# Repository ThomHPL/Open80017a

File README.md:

# Open80017a: an Open Source 80017a Roland Clone
<table>
  <tr>
    <td align="center"><b>Top View</b><br></td>
    <td align="center"><b>Bottom View</b><br></td>
  </tr>
</table>

## Context
The 80017a is a VCF/VCA module encapsulated in resin, used in the voices of various vintage Roland synthesizers such as the Juno-106. These modules are known to fail over time, potentially due to the resin coating.

## Open Source Aftermarket Replacement
While some clone modules are available for sale, they are often hard to find or relatively expensive. To be 100% honest, this project is also mostly a learning opportunity for me in vintage analog synth design.

### Key Design Focus Points
- **EMC Best Practices**
    - 4-layer PCB design
    - Proper trace spacing
- **Thermal Stability**
    - Vias under the OTAs to (try to) thermally couple them using an internal ground plane
- **Miniaturization**
    - Tries to match the original module dimensions

### Schematic

### Production
While the project uses a 4-layer board design, it has not requirements considering impedance control. It can therefore be made with any cheap 4-layer online service.

## Tests
Version 0.1 was assembled and tested in a Juno-106, with no perceivable difference (to my ears) between the clone and the original voices. However, there was an error in the buffer PMOS footprint, which was corrected with bodge wires.

Version 0.2 fixes the footprints. It has not yet been assembled or tested.

## Support

If you like my work, you can contribute with a coffee there ;)

## Credits
- This work was motivated by a dead channel on my brother's Juno-106. Thanks for the opportunity to help bro'!
- It would not have been possible without resources found online, especially the information provided by **dksynth** and **guest** on the following forum. Many thanks to them! [https://modwiggler.com/forum/viewtopic.php?t=238335](https://modwiggler.com/forum/viewtopic.php?t=238335)
- Thanks to [**deanm1278**](https://github.com/deanm1278) for the [LM13700 spice model](https://github.com/deanm1278/LM13700-spice-model).
- A lot of good info there as well: [80017A VCF/VCA Teardown](https://obsoletetechnology.wordpress.com/projects/80017a-vcfvca-teardown/)

## Disclaimer

While I did my best to provide a good quality design and I performed a simple test of the design, this project is provided as-is, without any warranty or guarantee. I am not responsible for any damage, malfunction, or harm caused to your hardware, equipment, or any other property resulting from the use, assembly, or modification of this project. Use at your own risk.

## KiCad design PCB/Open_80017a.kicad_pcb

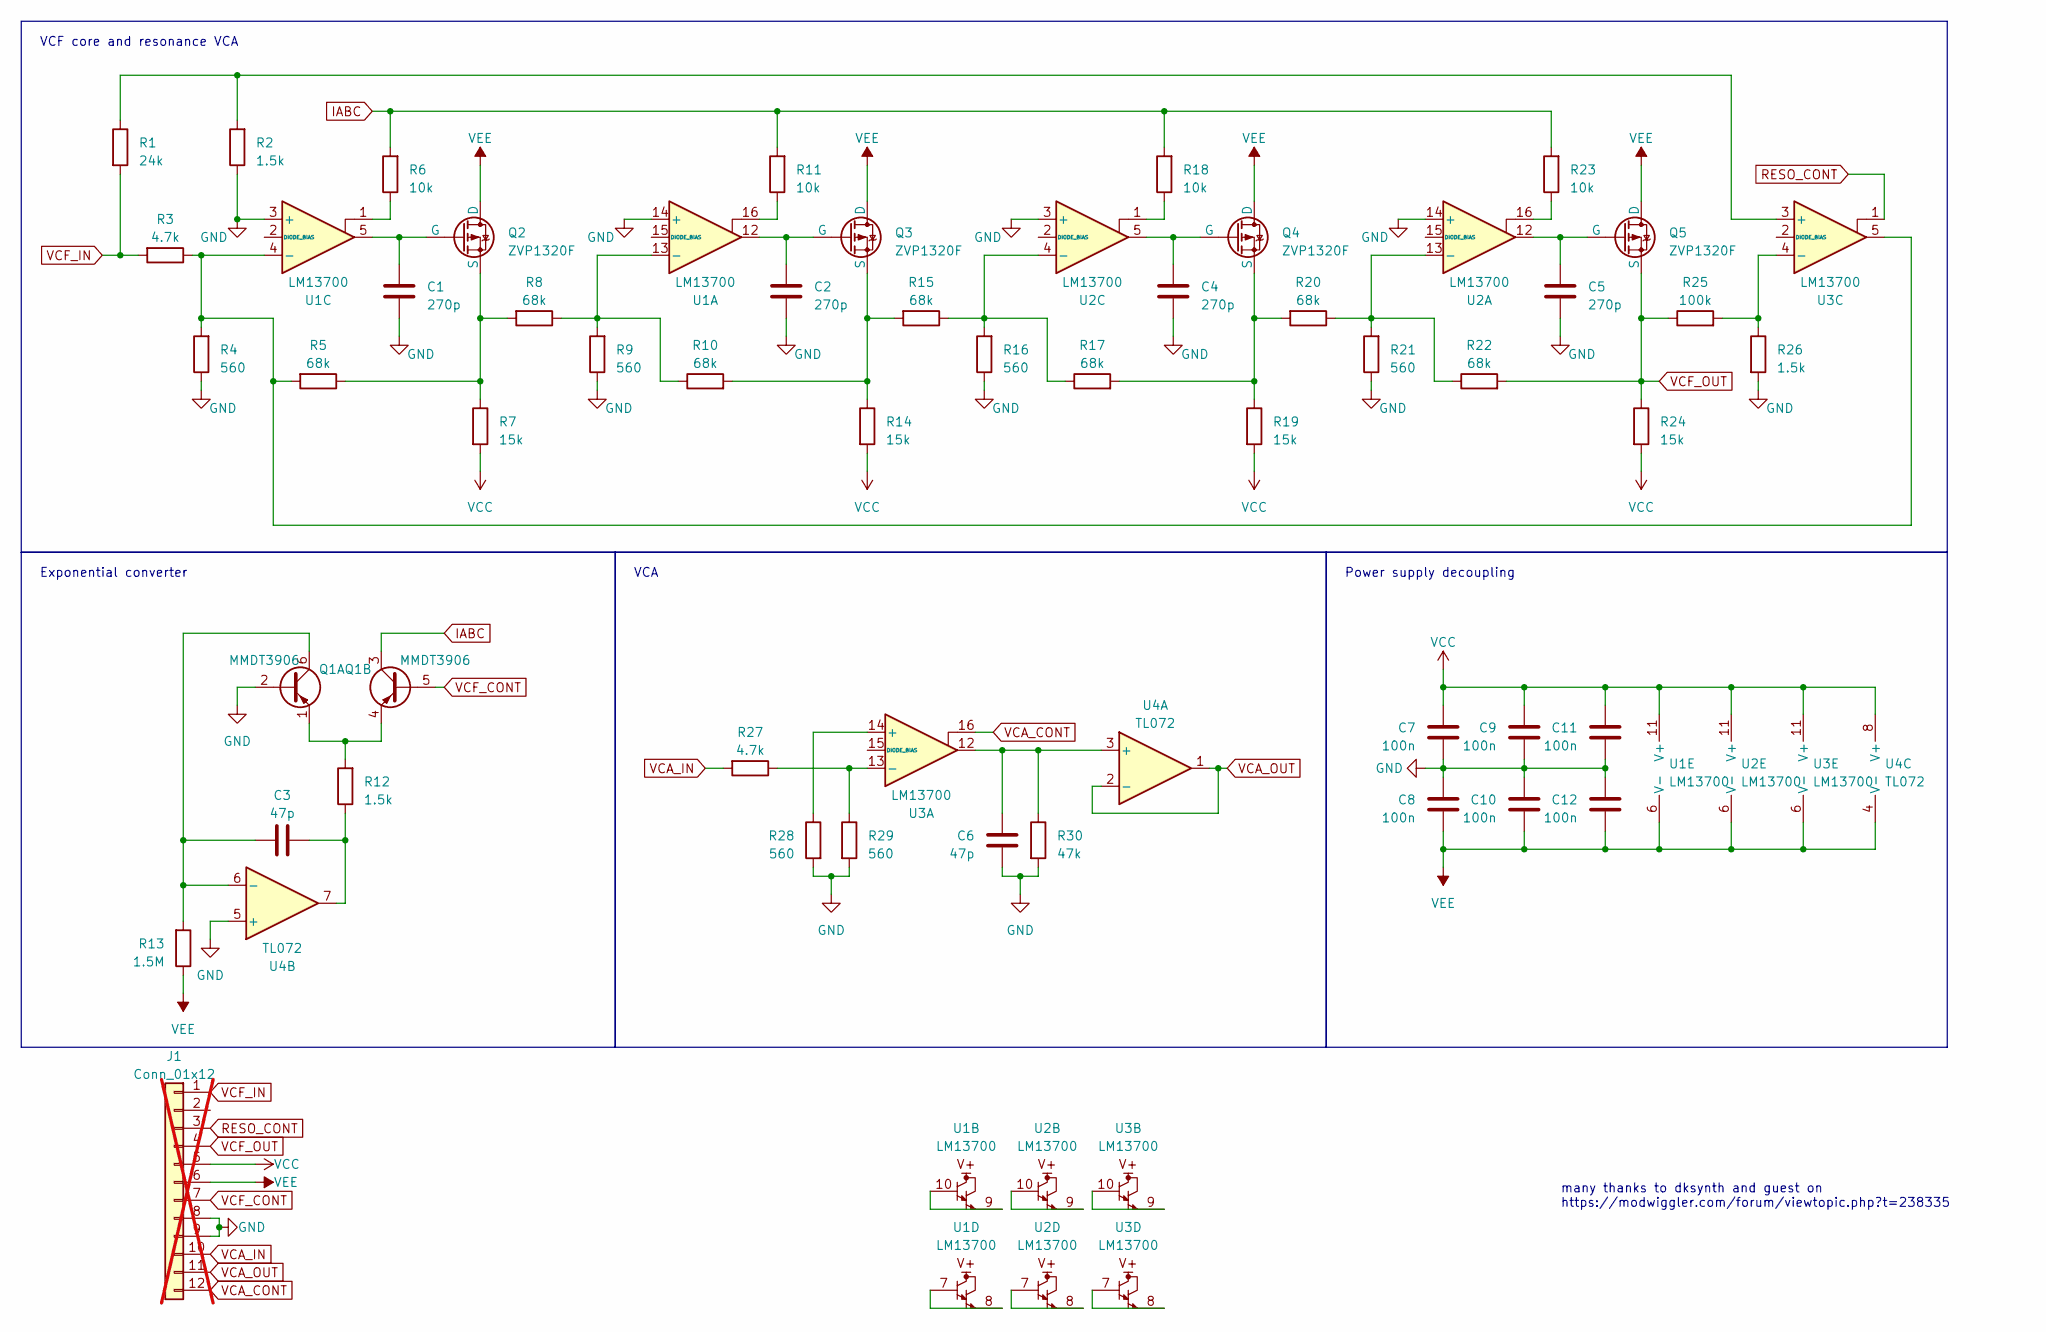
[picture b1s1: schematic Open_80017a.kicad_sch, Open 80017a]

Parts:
C1, C2, C4, C5: 270p; C_0603_1608Metric_Pad1.08x0.95mm_HandSolder
C3, C6: 47p; C_0603_1608Metric_Pad1.08x0.95mm_HandSolder
C7, C8, C9, C10, C11, C12: 100n; C_0603_1608Metric_Pad1.08x0.95mm_HandSolder
J1: Conn_01x12; PinHeader_1x12_P2.54mm_Horizontal; not fitted
Q1: MMDT3906; SOT-363_SC-70-6
Q2, Q3, Q4, Q5: ZVP1320F; TSOT-23
R1: 24k; R_0603_1608Metric_Pad0.98x0.95mm_HandSolder
R2, R12, R26: 1.5k; R_0603_1608Metric_Pad0.98x0.95mm_HandSolder
R3, R27: 4.7k; R_0603_1608Metric_Pad0.98x0.95mm_HandSolder
R4, R9, R16, R21, R28, R29: 560; R_0603_1608Metric_Pad0.98x0.95mm_HandSolder
R5, R8, R10, R15, R17, R20, R22: 68k; R_0603_1608Metric_Pad0.98x0.95mm_HandSolder
R6, R11, R18, R23: 10k; R_0603_1608Metric_Pad0.98x0.95mm_HandSolder
R7, R14, R19, R24: 15k; R_0603_1608Metric_Pad0.98x0.95mm_HandSolder
R13: 1.5M; R_0603_1608Metric_Pad0.98x0.95mm_HandSolder
R25: 100k; R_0603_1608Metric_Pad0.98x0.95mm_HandSolder
R30: 47k; R_0603_1608Metric_Pad0.98x0.95mm_HandSolder
U1, U2, U3: LM13700; SOIC-16_3.9x9.9mm_P1.27mm; mouser 926-LM13700M/NOPB
U4: TL072; TSSOP-8_4.4x3mm_P0.65mm

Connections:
GND: C1.2, C2.1, C4.1, C5.1, C6.1, C7.1, C8.2, C9.1, C10.2, C11.1, C12.2, J1.8, J1.9, Q1.2 (B1), R2.1, R4.1, R9.1, R16.1, R21.1, R26.2, R28.2, R29.2, R30.2, U1.3 (+), U1.14 (+), U2.3 (+), U2.14 (+), U4.5 (+)
IABC: Q1.3 (C2), R6.2, R11.2, R18.2, R23.2
unnamed: C3.2, R12.1, U4.7
unnamed: C3.1, Q1.6 (C1), R13.2, U4.6 (-)
unnamed: Q1.1 (E1), Q1.4 (E2), R12.2
unnamed: C1.1, Q2.2 (G), U1.5
unnamed: Q2.3 (S), R5.1, R7.1, R8.2
unnamed: C2.2, Q3.2 (G), U1.12
unnamed: Q3.3 (S), R10.2, R14.1, R15.2
unnamed: C4.2, Q4.2 (G), U2.5
unnamed: Q4.3 (S), R17.2, R19.1, R20.2
unnamed: C5.2, Q5.2 (G), U2.12
unnamed: R6.1, U1.1
unnamed: R11.1, U1.16
unnamed: R18.1, U2.1
unnamed: R23.1, U2.16
unnamed: U1.7, U1.8
unnamed: U1.9, U1.10
unnamed: R8.1, R9.2, R10.1, U1.13 (-)
unnamed: R3.1, R4.2, R5.2, U1.4 (-), U3.5
unnamed: U2.7, U2.8
unnamed: U2.9, U2.10
unnamed: R20.1, R21.2, R22.1, U2.13 (-)
unnamed: R15.1, R16.2, R17.1, U2.4 (-)
unnamed: U3.7, U3.8
unnamed: U3.9, U3.10
unnamed: R28.1, U3.14 (+)
unnamed: R27.1, R29.1, U3.13 (-)
unnamed: R1.1, R2.2, U3.3 (+)
unnamed: R25.2, R26.1, U3.4 (-)
unnamed: C6.2, R30.1, U3.12, U4.3 (+)
RESO_CONT: J1.3, U3.1
VCA_CONT: J1.12, U3.16
VCA_IN: J1.10, R27.2
VCA_OUT: J1.11, U4.1, U4.2 (-)
VCC: C7.2, C9.2, C11.2, J1.5, R7.2, R14.2, R19.2, R24.2, U1.11 (V+), U2.11 (V+), U3.11 (V+), U4.8 (V+)
VCF_CONT: J1.7, Q1.5 (B2)
VCF_IN: J1.1, R1.2, R3.2
VCF_OUT: J1.4, Q5.3 (S), R22.2, R24.1, R25.1
VEE: C8.1, C10.1, C12.1, J1.6, Q2.1 (D), Q3.1 (D), Q4.1 (D), Q5.1 (D), R13.1, U1.6 (V-), U2.6 (V-), U3.6 (V-), U4.4 (V-)

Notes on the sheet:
VCA
Power supply decoupling
Exponential converter
many thanks to dksynth and guest on https://modwiggler.com/forum/viewtopic.php?t=238335
VCF core and resonance VCA

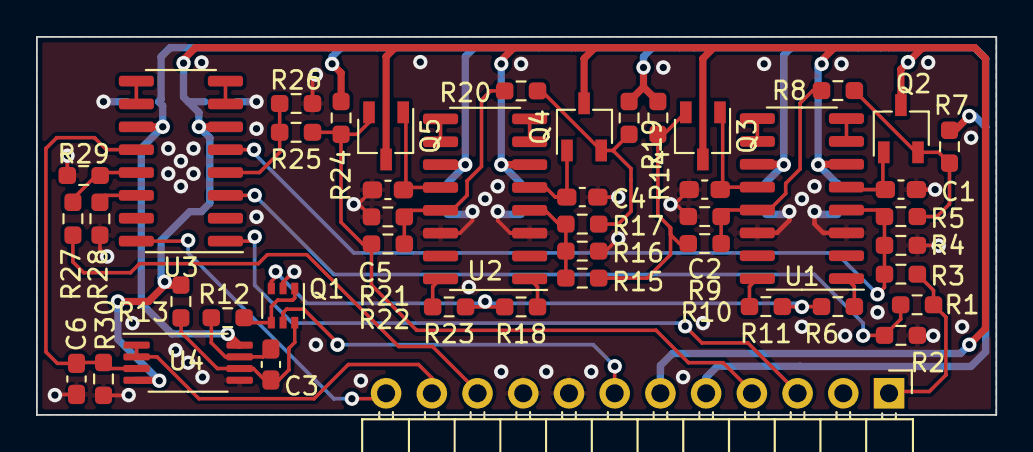
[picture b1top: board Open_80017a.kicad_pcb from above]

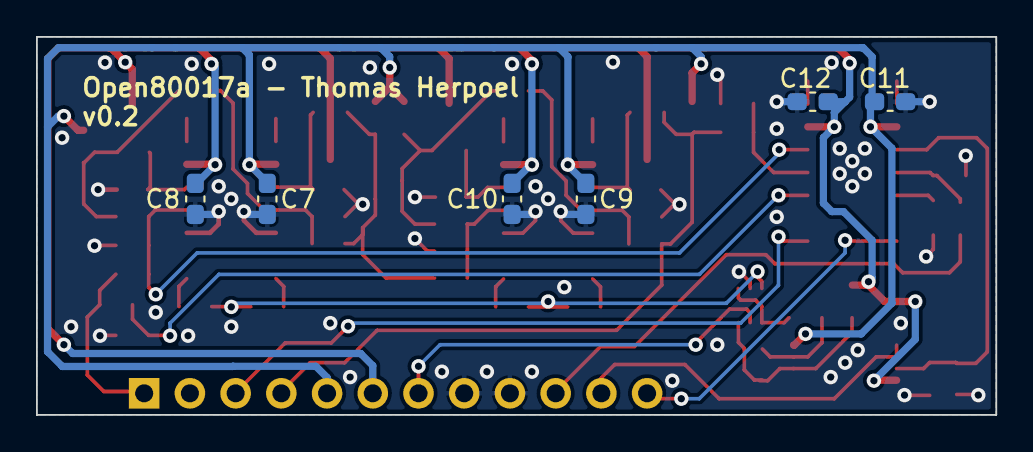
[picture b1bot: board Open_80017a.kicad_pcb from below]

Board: 4 copper layers, 53.3 x 21.0 mm, 52 parts (6 on the bottom side), 40 nets.

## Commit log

2025-06-04 licensed under CERN-OHL-S
2025-06-04 project info
2025-06-04 adding schematic
2025-06-04 adding svg
2025-06-04 fix svg
2025-06-04 using raw link for svg
2025-06-04 adding schematic pdf
2025-06-04 add download link for schematic
2025-06-04 images size
2025-06-04 PCB design
2025-06-04 simulations
2025-06-04 add interactive bom as github page
2025-06-05 adding credits
2025-06-05 more info on vcf
2025-06-05 fix pdf link
2025-06-05 adding funding
2025-06-05 changing funding
2025-06-06 fix .prl
